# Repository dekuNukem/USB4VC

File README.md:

# USB4VC: USB Inputs on Retro Computers!

[Get USB4VC!](https://www.tindie.com/products/dekuNukem/usb4vc-usb-inputs-on-retro-computers/) | [Official Discord](https://discord.gg/HAuuh3pAmB) | [Getting Started](getting_started.md) | [Table of Contents](#table-of-contents)

-----

USB4VC is an **active protocol converter** that let you use **USB keyboard, mouse, and gamepads** on many different retro computers.

With a **modular design**, different platforms are supported by swapping out **Protocol Cards**:

USB4VC is [now available on Tindie](https://www.tindie.com/products/dekuNukem/usb4vc-usb-inputs-on-retro-computers/), with two Protocol Cards:

#### IBM PC Compatible

* PS/2 Keyboard (Scancode set 1, 2 and 3)
* PS/2 Mouse
* AT Keyboard
* XT Keyboard
* Microsoft Serial Mouse
* Mouse Systems Serial Mouse
* 15-pin Gameport Gamepad
* Mapping USB Gamepad to PC Mouse/Keyboard

From the very first IBM PC in 1981 until the end of PS/2 ports in early 2000s, this Protocol Card covers it all!

#### Apple Lisa, Early Macintosh, and Apple Desktop Bus (ADB)

* Apple Lisa Keyboard (A6MB101)
* Apple Lisa Mouse (A9M0050)
* Macintosh Keyboard (M0110A)
* Macintosh Mouse (M0100)
* ADB Keyboard
* ADB Mouse
* Mapping USB gamepad to all above

From Apple Lisa in 1983 to PowerMac G3 in 1999, and everything in-between!

#### More to Come!

Of course, more Protocol Cards are planned, and you can try [make your own](technical_notes.md) too!

## I Want One! / Get in Touch

USB4VC is now available [on my Tindie store](https://www.tindie.com/products/dekuNukem/usb4vc-usb-inputs-on-retro-computers/) after being successfully funded [on Kickstarter!](https://www.kickstarter.com/projects/dekunukem/usb4vc-usb-inputs-on-retro-computers)!

**Questions or comments?** Ask in [official Discord](https://discord.gg/HAuuh3pAmB), raise a [Github issue](https://github.com/dekuNukem/USB4VC/issues), [Twitter DM](https://twitter.com/dekuNukem_), or email `dekunukem` `gmail.com`!

## Videos

* [LGR Review](https://www.youtube.com/watch?v=tbHr7ULpusM)

* [Michael MJD Review](https://www.youtube.com/watch?v=Hv4A9p7Cn2s)

* [1Bit Fever Dreams review of Lisa/Mac/ADB card](https://youtu.be/ALm5LWS0fqU)

## Highlights

* USB Keyboard/Mouse/Gamepads on Vintage Computers!

* Modular & Swappable Protocol Cards

* Wireless / Bluetooth

* Ultra Low Latency (0.5ms)

* Fully Open-source

* Make-your-own Protocol Card [Instruction Provided](technical_notes.md)

## How it Works

USB4VC consists of two halves: **Baseboard** and swappable **Protocol Cards**.

Baseboard contains user buttons, OLED screen, and a Raspberry Pi. It processes USB input events, which are sent to Protocol Card.

Each Protocol Card has a dedicated microcontroller and connectors for a specific platform.

By splitting duties, RPi can focus on input parsing, and Protocol Card handles timing critical signal generation, resulting in a flexible architecture and reliable performance.

USB peripherals can be connected via cables, wireless dongles, or Bluetooth.

## Getting Started

[Click me](getting_started.md)

## Technical Details / Make Your Own Protocol Cards

[Click me](technical_notes.md)

## Why / Project Goals

Before the homogeneity of USB peripherals today, computer input devices were a wild west of proprietary peripherals, as different platforms used their own connectors and protocols for keyboards, mice, and gamepads.

With the popularity of retro computing today, it poses several issues:

* Many of those peripherals are simply **hard to find**, commanding a premium on online marketplaces. They are only getting rarer, and without them, the computer itself is useless.

* After decades of service, many can be **degraded and unreliable** (e.g. foam & foil keyboards), requiring extensive restoration.

* Many early peripherals simply **does not feel that great**. Mushy membrane keyboards, sticky ball mice, plasticky gamepads, etc. And of course, the good ones gets [*very expensive*](https://www.ebay.com/sch/i.html?_nkw=ibm+model+f&_sacat=0&rt=nc&LH_Sold=1&LH_Complete=1).

* On the other hand, good quality USB peripherals can be had for a very reasonable price today with vastly **superior tactility, precision, and ergonomics**.

* Thus, this project aims to make retro computers simply **more enjoyable to use**.

* I also hope it can **lower the barrier of entry** for certain machines, put more computers **back in action**, help **preserving** existing peripherals, and generally **help more people** get into this hobby!

But of course, one can argue that using period-correct peripherals is simply part of the hobby, but just like HDMI upscalers or floppy emus, it's nice to have the option to enhance the experience.

## Q&A

### Where can I get one?

This project have been successly funded [via Kickstarter!](https://www.kickstarter.com/projects/dekunukem/usb4vc-usb-inputs-on-retro-computers), now it is available [on my Tindie store!](https://www.tindie.com/products/dekuNukem/usb4vc-usb-inputs-on-retro-computers/)

### Which Raspberry Pi can I use?

Any RPi with a **40-pin header** *should* work, although **Model B/B+** is preferred. See [this table](https://en.wikipedia.org/wiki/Raspberry_Pi#Model_comparison) for details, sort by **GPIO** column.

USB4VC has been officially tested on **Raspberry Pi 2/3/4 Model B**.

Raspberry Pi Zeros should work too, but would need a USB hub.

No need to get the latest and greatest. An older RPi is plenty fast enough!

### What about latency?

0.5ms to 1ms depending on the Raspberry Pi generation.

1ms is *one thousandth* of a second. [More info here](technical_notes.md#latency-information).

### Can you develop a Protocol Card for ___ ?

I'd love to! But I would need a working machine with working peripherals.

So if you're in UK and is happy to lend me one for a while, [let me know!](#i-want-one--get-in-touch)

Also, as I can only work on so many at once, I'll probably focus on the more popular machines at first, but still, do let me know!

### Can I make my own Protocol Cards?

Of course! See [this document](technical_notes.md).

### What does USB4VC stand for?

USB for Vintage Computers. Although come to think of it, it's perfect for vintage consoles too! 🤔

## Questions or Comments?

Feel free to ask in official [Discord Chatroom](https://discord.gg/HAuuh3pAmB), raise a [Github issue](https://github.com/dekuNukem/USB4VC/issues), [DM on Twitter](https://twitter.com/dekuNukem_), or email `dekunukem` `gmail.com`!

## Table of Contents

[Main page](README.md)

[(Youtube Video) USB4VC in Action](https://www.youtube.com/watch?v=54sdPELuu4g)

[Getting Started Guide](getting_started.md)

[Kit Assembly Guide](kit_assembly.md)

[Tinkering Guide / Make Your Own Protocol Card / Technical Notes](technical_notes.md)

[Kickstarter Acknowledgements](kickstarter_info.md)

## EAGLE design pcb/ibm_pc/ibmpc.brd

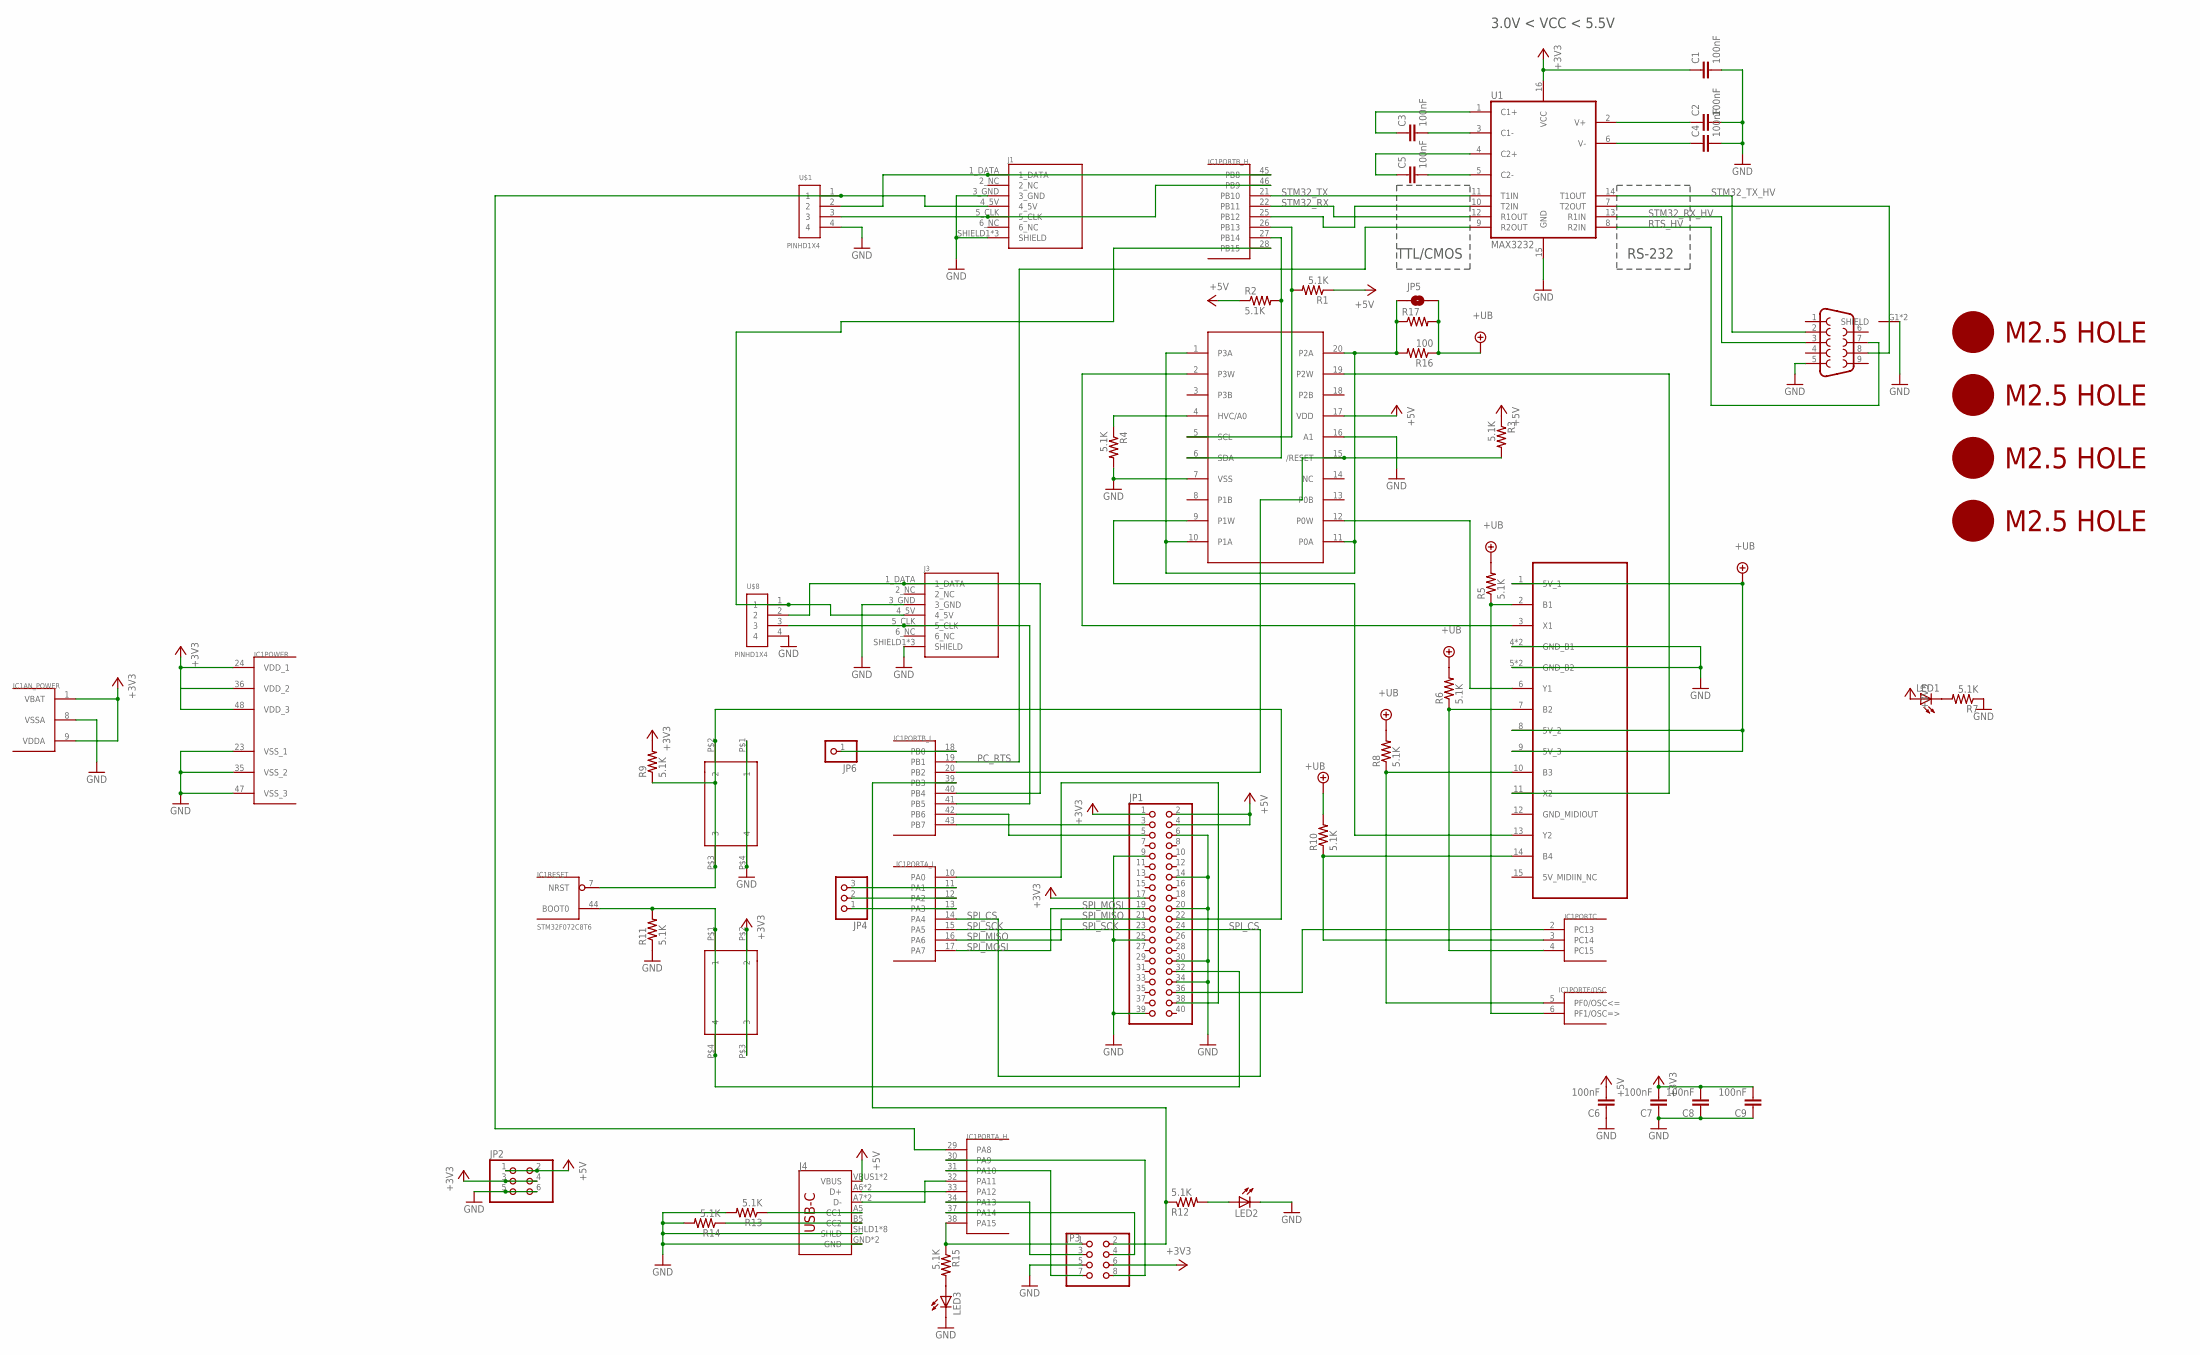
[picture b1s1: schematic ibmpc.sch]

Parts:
C1, C2, C3, C4, C5, C6, C7, C8, C9: 100nF; 0805@1
IC1: STM32F072C8T6; TQFP48
J1, J3: DIN7
J2: DB9MALE; DB9_MALE
J4: USB_C16PIN; USB-C-16P
JP1: PINHD-2X20-BIG; 2X20-BIG
JP2: PINHD-2X3; 2X03
JP3: PINHD-2X4; 2X04
JP4: PINHD-1X3CB; 1X03-CLEANBIG
JP5: JUMPER-SMT_2_NO_NO-SILK; SMT-JUMPER_2_NO_NO-SILK
JP6: PINHD-1X1CB; 1X01-CLEANBIG
LED1, LED2, LED3: LEDCHIP-LED0805; CHIP-LED0805
R1, R2, R3, R4, R5, R6, R7, R8, R9, R10, R11, R12, R13, R14, R15: 5.1K; 0805
R16: 100; 0805
R17: R-US_0204/7; 0204/7
SW1, SW2: 324_SW; 342_SWICH_FOOT
U1: MAX3232; SO016
U$1, U$8: PINHD1X4; 1X04-CLEANBIG
U$2, U$3, U$6, U$7: M2.5HOLE
U$5: MCP4451; TSSOP20
U$9: GAMEPORT_15P; DA15

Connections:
+3V3: C1.1, C7.2, C8.2, C9.2, IC1.1 (VBAT), IC1.9 (VDDA), IC1.24 (VDD_1), IC1.36 (VDD_2), IC1.48 (VDD_3), JP1.1, JP1.17, JP2.3, JP2.4, JP3.6, LED1.A, R9.2, SW2.P$2 (2), SW2.P$3 (3), U1.16 (VCC)
+5V: C6.2, J4.VBUS1 (VBUS), J4.VBUS2 (VBUS), JP1.2, JP1.4, JP2.1, JP2.2, R1.1, R2.1, R3.1, U$5.17 (VDD)
+UB: JP5.2, R5.2, R6.2, R8.2, R10.2, R16.1, R17.2, U$9.1 (5V_1), U$9.8 (5V_2), U$9.9 (5V_3)
C1+: C3.1, U1.1 (C1+)
C1-: C3.2, U1.3 (C1-)
C2+: C5.1, U1.4 (C2+)
C2-: C5.2, U1.5 (C2-)
GND: C1.2, C2.2, C4.2, C6.1, C7.1, C8.1, C9.1, IC1.8 (VSSA), IC1.23 (VSS_1), IC1.35 (VSS_2), IC1.47 (VSS_3), J1.3_GND, J1.SHIELD1 (SHIELD), J1.SHIELD2 (SHIELD), J1.SHIELD3 (SHIELD), J2.5, J2.G1 (SHIELD), J2.G2 (SHIELD), J3.3_GND, J3.SHIELD1 (SHIELD), J3.SHIELD2 (SHIELD), J3.SHIELD3 (SHIELD), J4.GND, J4.GND2 (GND), J4.SHLD1 (SHLD), J4.SHLD2 (SHLD), J4.SHLD3 (SHLD), J4.SHLD4 (SHLD), J4.SHLD5 (SHLD), J4.SHLD6 (SHLD), J4.SHLD7 (SHLD), J4.SHLD8 (SHLD), JP1.6, JP1.9, JP1.14, JP1.20, JP1.25, JP1.30, JP1.34, JP1.39, JP2.5, JP2.6, JP3.5, LED2.C, LED3.C, R4.2, R7.1, R11.1, R13.2, R14.2, SW1.P$1 (1), SW1.P$4 (4), U1.15 (GND), U$1.4, U$5.7 (VSS), U$5.16 (A1), U$8.4, U$9.4 (GND_B1), U$9.5 (GND_B2), U$9.G1 (GND_B1), U$9.G2 (GND_B2)
unnamed: J4.A5 (CC1), R13.1
unnamed: LED2.A, R12.2
unnamed: IC1.10 (PA0), JP1.38
unnamed: IC1.29 (PA8), J1.4_5V, U$1.1
unnamed: IC1.41 (PB5), J3.5_CLK, U$8.3
unnamed: IC1.39 (PB3), JP3.2, R12.1
unnamed: J4.B5 (CC2), R14.1
unnamed: IC1.33 (PA12), J4.A6 (D+), J4.B6 (D+)
unnamed: IC1.32 (PA11), J4.A7 (D-), J4.B7 (D-)
unnamed: IC1.45 (PB8), J1.1_DATA, U$1.2
unnamed: IC1.46 (PB9), J1.5_CLK, U$1.3
unnamed: IC1.31 (PA10), JP3.7
unnamed: IC1.7 (NRST), JP1.22, R9.1, SW1.P$2 (2), SW1.P$3 (3)
unnamed: IC1.30 (PA9), JP3.8
unnamed: IC1.34 (PA13), JP3.3
unnamed: IC1.37 (PA14), JP3.4
unnamed: JP5.1, R16.2, R17.1, U$5.1 (P3A), U$5.10 (P1A), U$5.11 (P0A), U$5.20 (P2A)
unnamed: IC1.44 (BOOT0), JP1.32, R11.2, SW2.P$1 (1), SW2.P$4 (4)
unnamed: IC1.4 (PC15), R6.1, U$9.7 (B2)
unnamed: IC1.5 (PF0/OSC<=), R8.1, U$9.10 (B3)
unnamed: IC1.3 (PC14), R10.1, U$9.14 (B4)
unnamed: IC1.42 (PB6), JP1.5
unnamed: IC1.43 (PB7), JP1.3
unnamed: IC1.25 (PB12), U1.10 (T2IN)
unnamed: J2.8, U1.7 (T2OUT)
unnamed: IC1.40 (PB4), J3.1_DATA, U$8.2
unnamed: IC1.38 (PA15), JP3.1, R15.1
unnamed: LED3.A, R15.2
unnamed: LED1.C, R7.2
unnamed: IC1.18 (PB0), JP6.1
unnamed: IC1.6 (PF1/OSC=>), R5.1, U$9.2 (B1)
unnamed: R4.1, U$5.4 (HVC/A0)
unnamed: IC1.2 (PC13), JP1.36
unnamed: IC1.11 (PA1), JP4.3
unnamed: IC1.12 (PA2), JP4.2
unnamed: IC1.13 (PA3), JP4.1
unnamed: IC1.28 (PB15), J3.4_5V, U$8.1
unnamed: IC1.20 (PB2), R3.2, U$5.15 (/RESET)
PC_RTS: IC1.19 (PB1), U1.9 (R2OUT)
POT_SCL: IC1.26 (PB13), R1.2, U$5.5 (SCL)
PST_SDA: IC1.27 (PB14), R2.2, U$5.6 (SDA)
RTS_HV: J2.7, U1.8 (R2IN)
SPI_CS: IC1.14 (PA4), JP1.24
SPI_MISO: IC1.16 (PA6), JP1.21
SPI_MOSI: IC1.17 (PA7), JP1.19
SPI_SCK: IC1.15 (PA5), JP1.23
STM32_RX: IC1.22 (PB11), U1.12 (R1OUT)
STM32_RX_HV: J2.3, U1.13 (R1IN)
STM32_TX: IC1.21 (PB10), U1.11 (T1IN)
STM32_TX_HV: J2.2, U1.14 (T1OUT)
V+: C2.1, U1.2 (V+)
V-: C4.1, U1.6 (V-)
X1_W3: U$5.2 (P3W), U$9.3 (X1)
X2_W2: U$5.19 (P2W), U$9.11 (X2)
Y1_W0: U$5.12 (P0W), U$9.6 (Y1)
Y2_W1: U$5.9 (P1W), U$9.13 (Y2)

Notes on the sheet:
RS-232
TTL/CMOS
3.0V < VCC < 5.5V

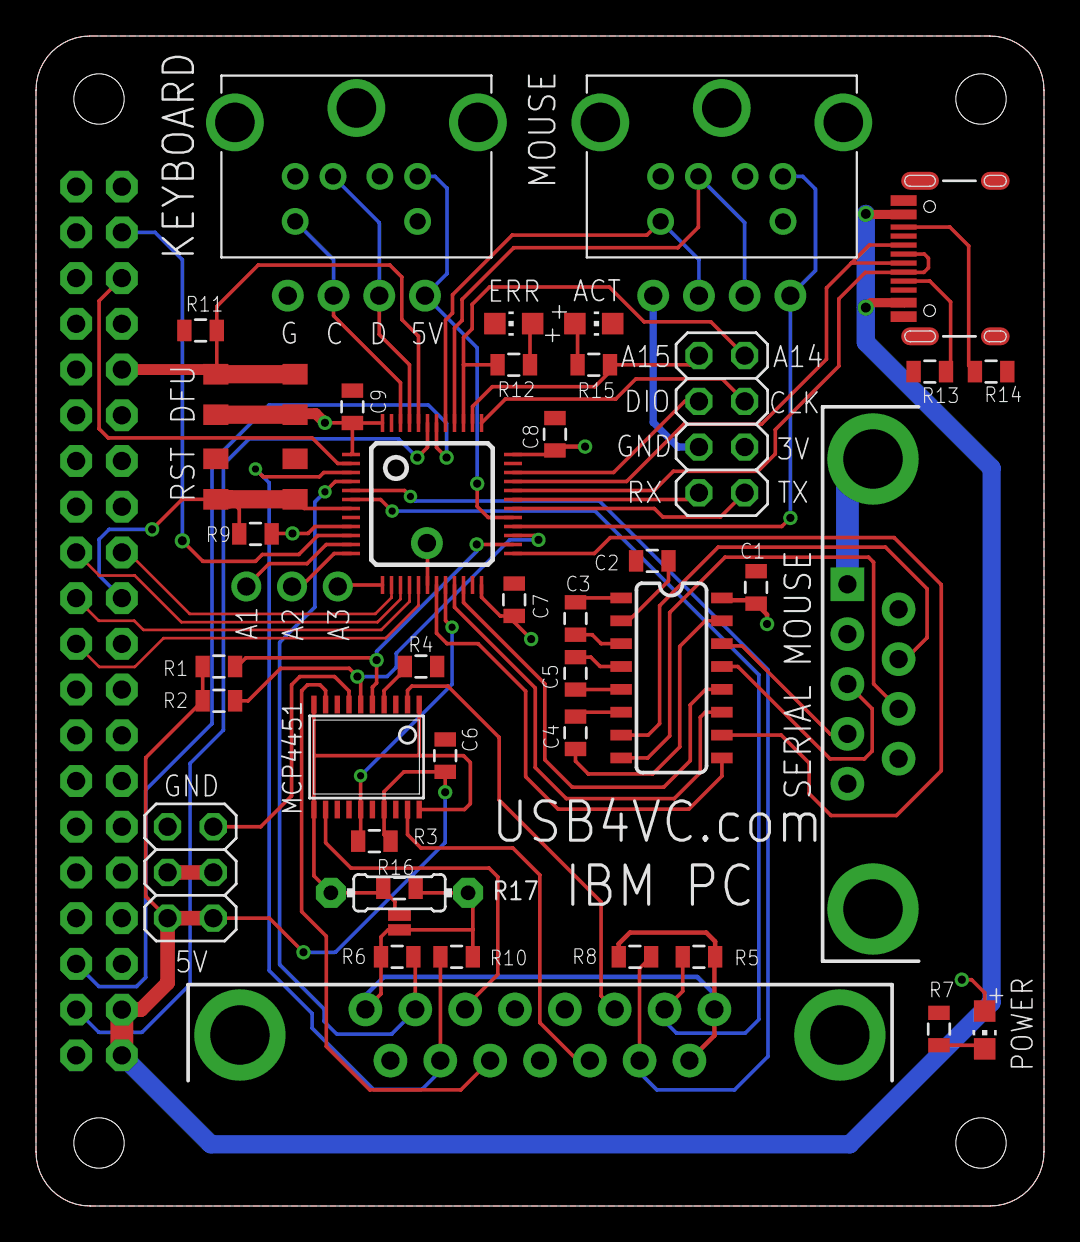
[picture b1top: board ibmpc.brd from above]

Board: 2 copper layers, 56.0 x 65.0 mm, 51 parts (1 on the bottom side), 64 nets.

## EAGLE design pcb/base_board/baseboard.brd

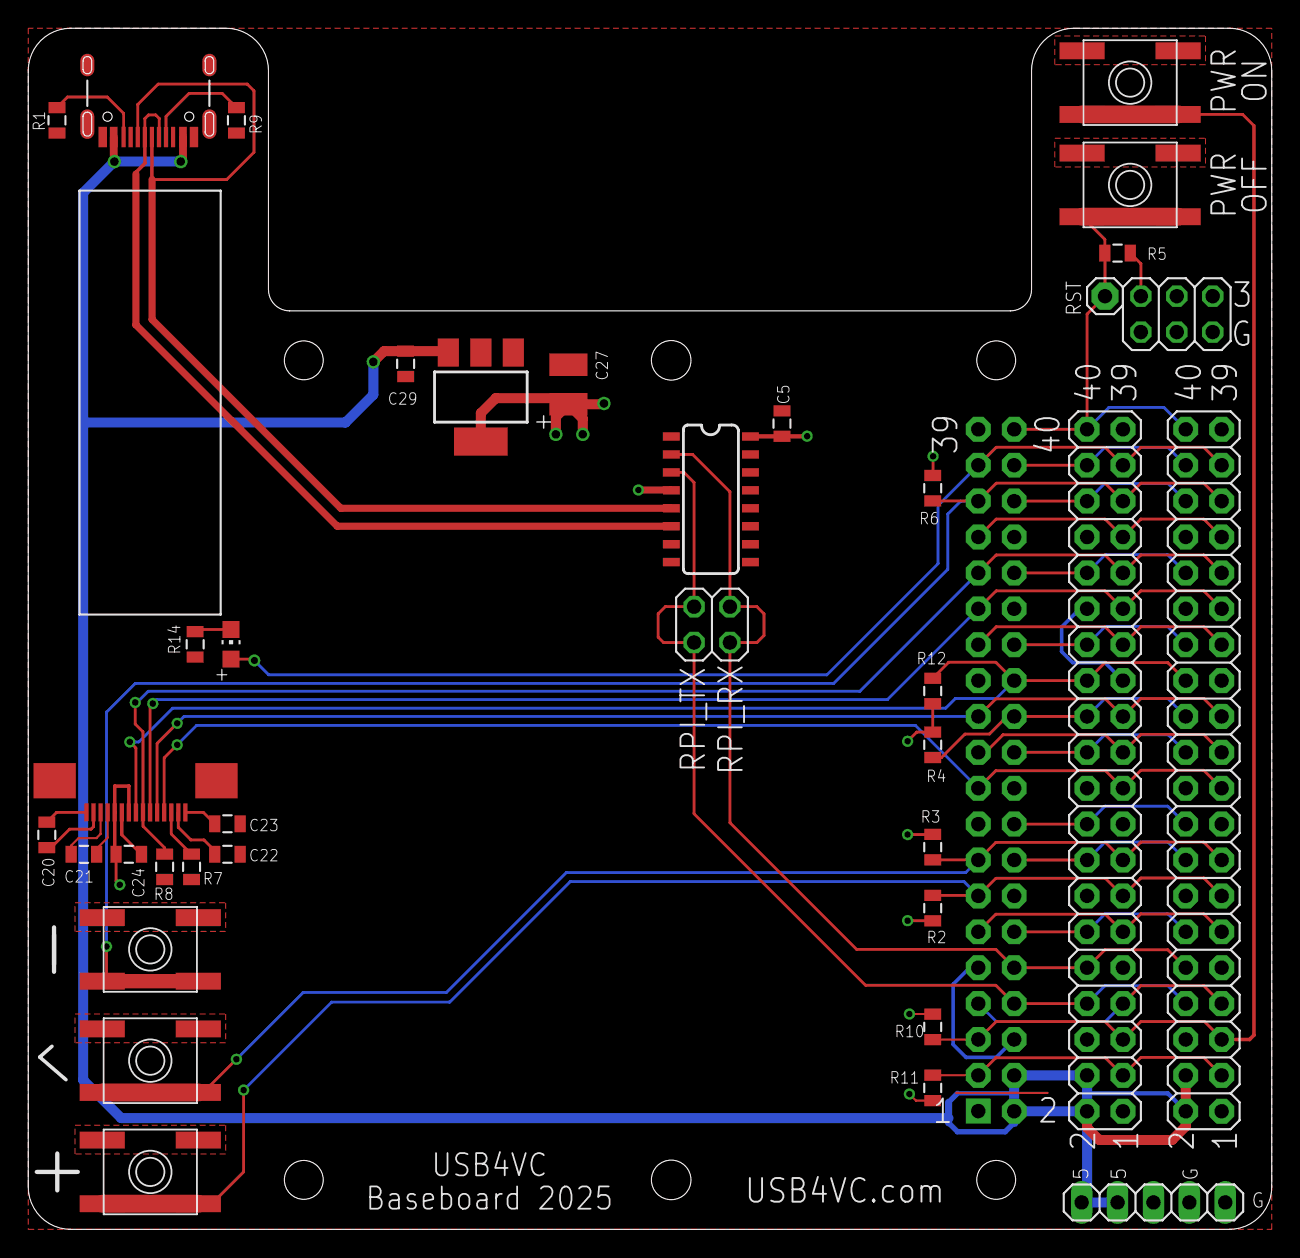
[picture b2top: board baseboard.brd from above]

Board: 2 copper layers, 88.0 x 85.0 mm, 40 parts (0 on the bottom side), 43 nets.

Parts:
C5, C24: 100nF; 0805
C20, C21: 1uF; 0805
C22, C23, C29: 2.2uF; 0805
C27: 47uF; C1210
IC1: LD117AS33TR; SOT223
J2: USB-C-16P
JP3: 1X01
JP5: 1X05
JP6: 2X03
JP7: 2X02
LED1: CHIP-LED0805
P1: RPI3NO-CONNECTORS; RPI3-NO-CONNECTORS
P2, P3: 2X20-BIG
R1, R2, R3, R4, R5, R6, R8, R9, R10, R11, R12: 5.1K; 0805
R7: 390K; 0805
R14: 2K; 0805
SW2, SW5, SW6, SW7, SW8: SPST_TACT-EVQQ2; EVQ-Q2
U2: LUL_UG-2864HSWEG01_1.3_WRAPAROUND
U5: CH340C; SO016
U$2, U$3: M2.5HOLE

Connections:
+3V3: C5.2, C24.2, C27.1, IC1.4, JP6.2, JP6.4, JP6.6, P2.1, P2.17, P3.1, P3.17, R2.2, R3.2, R4.1, R5.2, R6.2, R10.1, R11.1, R12.1, U2.5, U2.7, U5.4, U5.16
+5V: C29.2, IC1.3, J2.VBUS1, J2.VBUS2, JP5.1, JP5.2, P1.P$2, P1.P$4, P2.2, P2.4, P3.2, P3.4
ENTER_BUTTON: P1.P$15, P2.15, P3.15, R3.1, SW6.A, SW6.A'
GND: C5.1, C22.1, C23.1, C24.1, C27.2, C29.1, IC1.1, J2.GND, J2.GND2, J2.SHLD1, J2.SHLD2, J2.SHLD3, J2.SHLD4, J2.SHLD5, J2.SHLD6, J2.SHLD7, J2.SHLD8, JP5.4, JP5.5, JP6.1, JP6.3, JP6.5, P1.P$6, P1.P$9, P1.P$14, P1.P$20, P1.P$25, P1.P$30, P1.P$34, P1.P$39, P2.6, P2.9, P2.14, P2.20, P2.25, P2.30, P2.34, P2.39, P3.6, P3.9, P3.14, P3.20, P3.25, P3.30, P3.34, P3.39, R1.2, R7.1, R8.2, R9.2, R14.1, SW2.A, SW2.A', SW5.B, SW5.B', SW6.B, SW6.B', SW7.B, SW7.B', SW8.B, SW8.B', U2.6, U2.16, U2.17, U5.1
MINUS_BUTTON: P1.P$35, P2.35, P3.35, R6.1, SW5.A, SW5.A'
unnamed: J2.A6, J2.B6, U5.5
unnamed: J2.A5, R9.1
unnamed: J2.A7, J2.B7, U5.6
unnamed: LED1.A, P1.P$37, P2.37, P3.37
unnamed: P1.P$3, P2.3, P3.3, R11.2
unnamed: P1.P$5, P2.5, P3.5, R10.2, SW8.A, SW8.A'
unnamed: J2.B5, R1.1
unnamed: P1.P$7, P2.7, P3.7
unnamed: P1.P$11, P2.11, P3.11
unnamed: LED1.C, R14.2
unnamed: P1.P$19, P2.19, P3.19, U2.12
unnamed: P1.P$21, P2.21, P3.21
unnamed: P1.P$23, P2.23, P3.23, U2.11
unnamed: P1.P$27, P2.27, P3.27
unnamed: P1.P$29, P2.29, P3.29, U2.10
unnamed: P1.P$33, P2.33, P3.33
unnamed: P1.P$12, P2.12, P3.12
unnamed: P1.P$16, P2.16, P3.16
unnamed: P1.P$18, P2.18, P3.18
unnamed: P1.P$22, P2.22, P3.22
unnamed: P1.P$24, P2.24, P3.24, R4.2
unnamed: P1.P$26, P2.26, P3.26, R12.2, U2.8
unnamed: P1.P$28, P2.28, P3.28
unnamed: P1.P$32, P2.32, P3.32
unnamed: P1.P$36, P2.36, P3.36
unnamed: P1.P$38, P2.38, P3.38
unnamed: JP3.1, P1.P$40, P2.40, P3.40, R5.1, SW2.B, SW2.B'
unnamed: C20.2, U2.1
unnamed: C20.1, U2.2
unnamed: C21.2, U2.3
unnamed: C21.1, U2.4
unnamed: R7.2, U2.13
unnamed: C22.2, U2.14
unnamed: C23.2, U2.15
unnamed: P1.P$31, P2.31, P3.31, R8.1, U2.9
PLUS_BUTTON: P1.P$13, P2.13, P3.13, R2.1, SW7.A, SW7.A'
RPI_RX: JP7.1, JP7.2, P1.P$10, P2.10, P3.10, U5.2
RPI_TX: JP7.3, JP7.4, P1.P$8, P2.8, P3.8, U5.3

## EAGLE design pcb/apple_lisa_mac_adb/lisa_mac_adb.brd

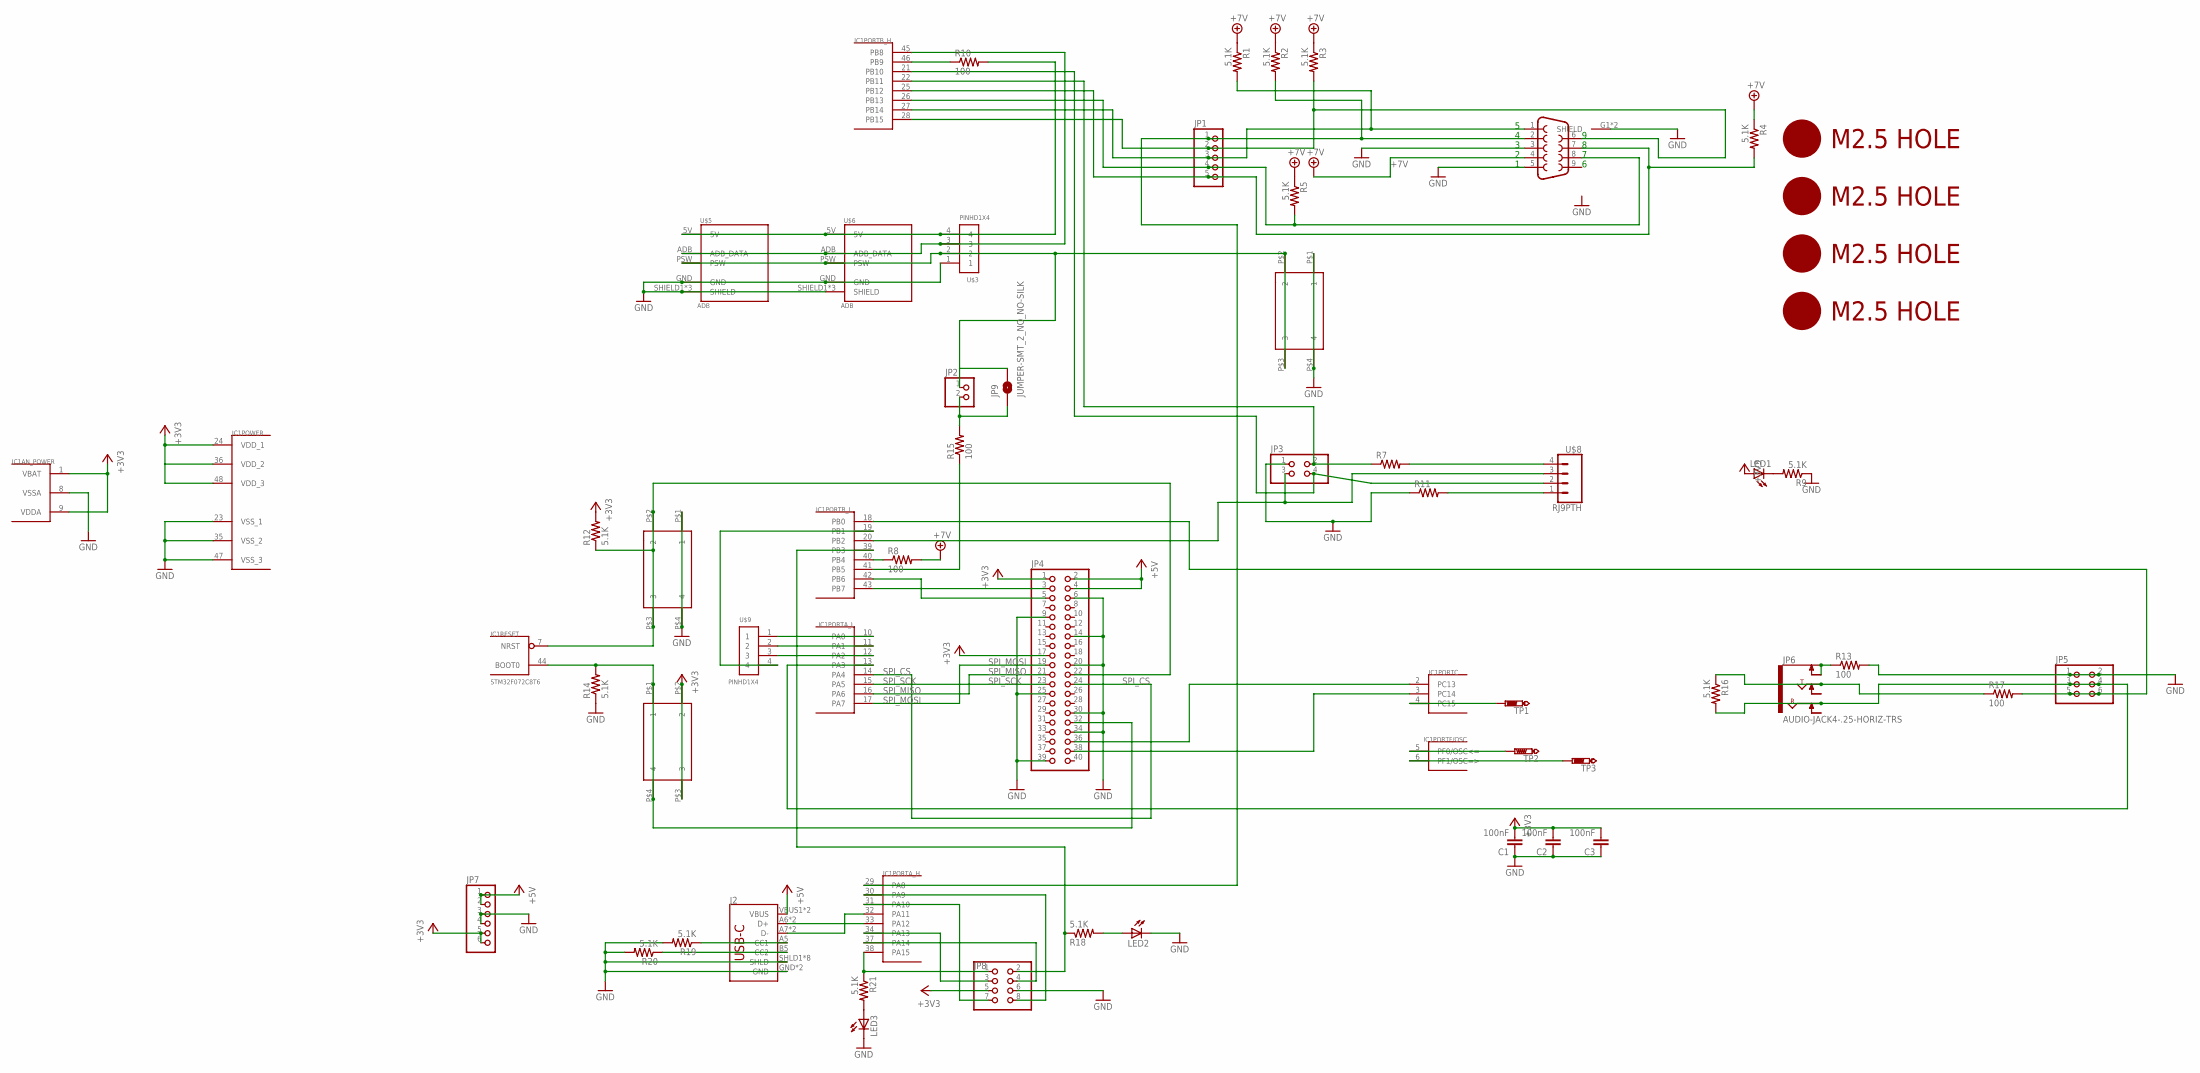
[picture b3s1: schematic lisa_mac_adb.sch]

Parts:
C1, C2, C3: 100nF; 0805@1
IC1: STM32F072C8T6; TQFP48
J1: DB9FEMALE; DB9
J2: USB_C16PIN; USB-C-16P
JP1: PINHD-1X5; 1X05
JP2: PINHD-1X2; 1X02
JP3: PINHD-2X2; 2X02
JP4: PINHD-2X20-BIG; 2X20-BIG
JP5: PINHD-2X3; 2X03
JP6: AUDIO-JACK4-.25-HORIZ-TRS; AUDIO-JACK-.25-INCH-HORIZ-PTH
JP7: PINHD-1X6CB; 1X06-CLEANBIG
JP8: PINHD-2X4; 2X04
JP9: JUMPER-SMT_2_NO_NO-SILK; SMT-JUMPER_2_NO_NO-SILK
LED1, LED2, LED3: LEDCHIP-LED0805; CHIP-LED0805
R1, R2, R3, R4, R5, R9, R12, R14, R16, R18, R19, R20, R21: 5.1K; 0805
R7, R8, R10, R11, R13, R15, R17: 100; 0805
SW1, SW2, SW3: 324_SW; 342_SWICH_FOOT
TP1, TP2, TP3: PTR1TP14R; TP14R
U$1, U$2, U$4, U$7: M2.5HOLE
U$3, U$9: PINHD1X4; 1X04-CLEANBIG
U$5, U$6: ADB; DIN4
U$8: RJ9PTH; RJ9

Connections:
+3V3: C1.2, C2.2, C3.2, IC1.1 (VBAT), IC1.9 (VDDA), IC1.24 (VDD_1), IC1.36 (VDD_2), IC1.48 (VDD_3), JP4.1, JP4.17, JP7.5, JP7.6, JP8.5, LED1.A, R12.2, SW3.P$2 (2), SW3.P$3 (3)
+5V: J2.VBUS1 (VBUS), J2.VBUS2 (VBUS), JP4.2, JP4.4, JP7.1, JP7.2
+7V: J1.4, R1.1, R2.1, R3.1, R4.1, R5.1, R8.2
GND: C1.1, C2.1, C3.1, IC1.8 (VSSA), IC1.23 (VSS_1), IC1.35 (VSS_2), IC1.47 (VSS_3), J1.3, J1.5, J1.G1 (SHIELD), J1.G2 (SHIELD), J2.GND, J2.GND2 (GND), J2.SHLD1 (SHLD), J2.SHLD2 (SHLD), J2.SHLD3 (SHLD), J2.SHLD4 (SHLD), J2.SHLD5 (SHLD), J2.SHLD6 (SHLD), J2.SHLD7 (SHLD), J2.SHLD8 (SHLD), JP3.1, JP4.6, JP4.9, JP4.14, JP4.20, JP4.25, JP4.30, JP4.34, JP4.39, JP5.1, JP5.2, JP7.3, JP7.4, JP8.6, LED2.C, LED3.C, R9.1, R11.1, R13.2, R14.1, R19.2, R20.2, SW1.P$1 (1), SW1.P$4 (4), SW2.P$1 (1), SW2.P$4 (4), U$3.1, U$5.GND, U$5.SHIELD1 (SHIELD), U$5.SHIELD2 (SHIELD), U$5.SHIELD3 (SHIELD), U$6.GND, U$6.SHIELD1 (SHIELD), U$6.SHIELD2 (SHIELD), U$6.SHIELD3 (SHIELD)
unnamed: J2.A5 (CC1), R19.1
unnamed: LED2.A, R18.2
unnamed: R10.2, U$3.4, U$5.5V, U$6.5V
unnamed: IC1.26 (PB13), J1.8, JP1.4, R5.2
unnamed: R7.2, U$8.4
unnamed: IC1.39 (PB3), JP8.2, R18.1
unnamed: J2.B5 (CC2), R20.1
unnamed: IC1.33 (PA12), J2.A6 (D+), J2.B6 (D+)
unnamed: IC1.32 (PA11), J2.A7 (D-), J2.B7 (D-)
unnamed: IC1.41 (PB5), R15.1
unnamed: IC1.19 (PB1), U$9.4
unnamed: IC1.31 (PA10), JP8.7
unnamed: IC1.7 (NRST), JP4.22, R12.1, SW2.P$2 (2), SW2.P$3 (3)
unnamed: IC1.30 (PA9), JP8.8
unnamed: IC1.34 (PA13), JP8.3
unnamed: IC1.37 (PA14), JP8.4
unnamed: IC1.22 (PB11), JP3.2, R7.1
unnamed: IC1.44 (BOOT0), JP4.32, R14.2, SW3.P$1 (1), SW3.P$4 (4)
unnamed: IC1.21 (PB10), JP3.4, U$8.2
unnamed: IC1.4 (PC15), TP1.TP
unnamed: R11.2, U$8.1
unnamed: IC1.42 (PB6), JP4.5
unnamed: IC1.43 (PB7), JP4.3
unnamed: JP6.SLEEVE (EARTH), JP6.SLEEVE-NORM (EARTH-NORM), R13.1
unnamed: IC1.20 (PB2), JP3.3, U$8.3
unnamed: IC1.27 (PB14), J1.1, JP1.3, R1.2
unnamed: IC1.38 (PA15), JP8.1, R21.1
unnamed: LED3.A, R21.2
unnamed: LED1.C, R9.2
unnamed: IC1.13 (PA3), JP5.3, JP5.4, JP6.RING, R16.2
unnamed: IC1.18 (PB0), JP5.5, JP5.6, R17.2
unnamed: JP6.TIP, R16.1, R17.1
unnamed: IC1.3 (PC14), JP4.38
unnamed: IC1.28 (PB15), J1.6, JP1.2, R3.2
unnamed: IC1.25 (PB12), J1.7, JP1.5, R4.2
unnamed: IC1.29 (PA8), J1.2, JP1.1, R2.2
unnamed: IC1.2 (PC13), JP4.36
unnamed: IC1.10 (PA0), U$9.1
unnamed: IC1.11 (PA1), U$9.2
unnamed: IC1.12 (PA2), U$9.3
unnamed: IC1.5 (PF0/OSC<=), TP2.TP
unnamed: IC1.6 (PF1/OSC=>), TP3.TP
unnamed: IC1.45 (PB8), U$3.3, U$5.ADB (ADB_DATA), U$6.ADB (ADB_DATA)
unnamed: IC1.40 (PB4), R8.1
unnamed: IC1.46 (PB9), R10.1
unnamed: JP2.1, JP9.2, SW1.P$2 (2), SW1.P$3 (3), U$3.2, U$5.PSW, U$6.PSW
unnamed: JP2.2, JP9.1, R15.2
SPI_CS: IC1.14 (PA4), JP4.24
SPI_MISO: IC1.16 (PA6), JP4.21
SPI_MOSI: IC1.17 (PA7), JP4.19
SPI_SCK: IC1.15 (PA5), JP4.23

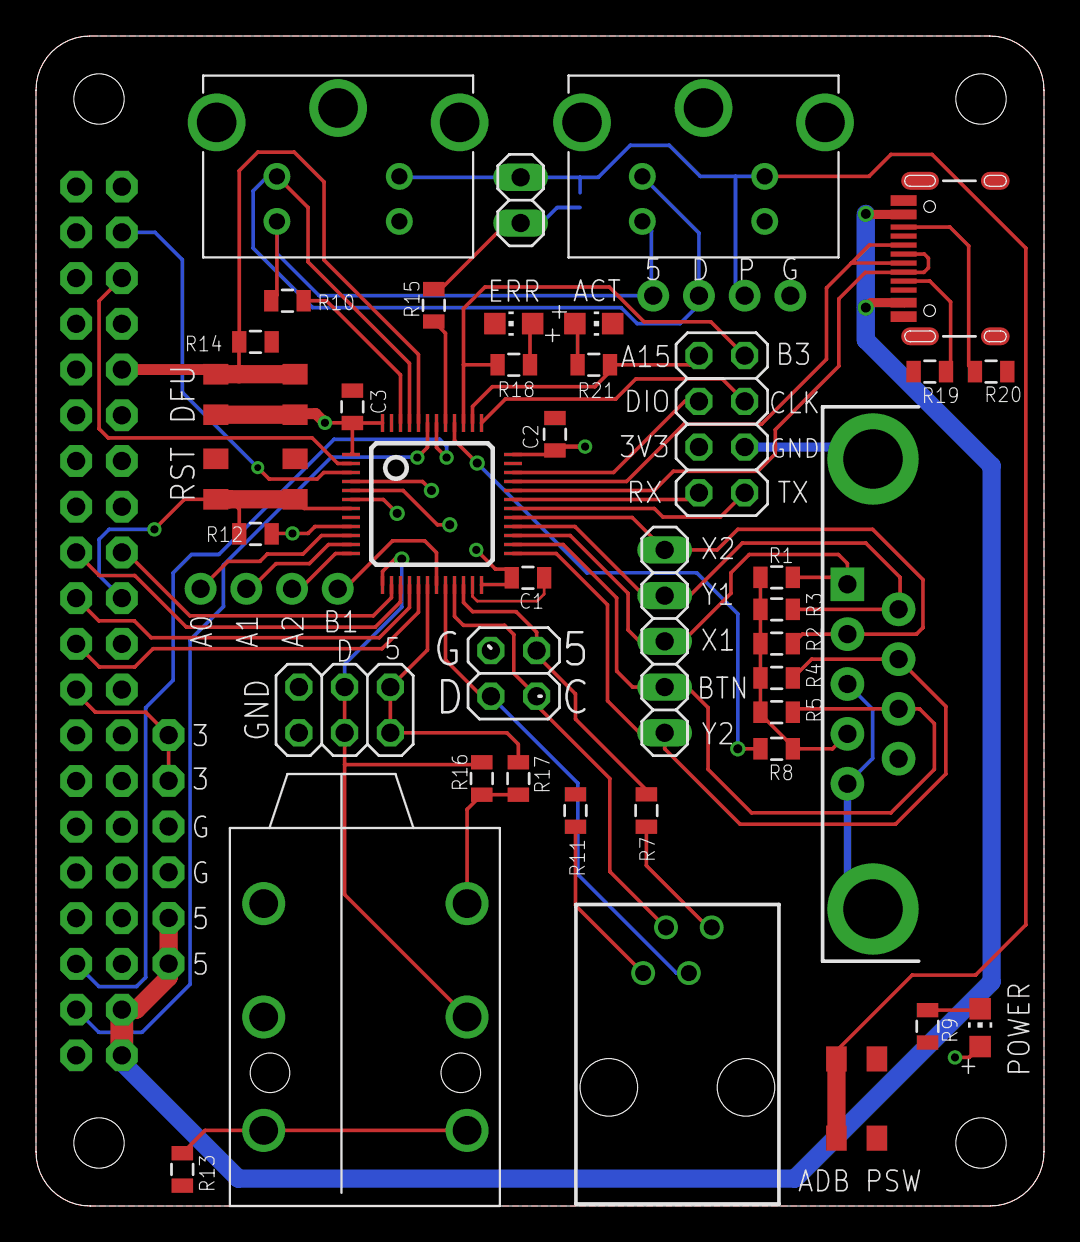
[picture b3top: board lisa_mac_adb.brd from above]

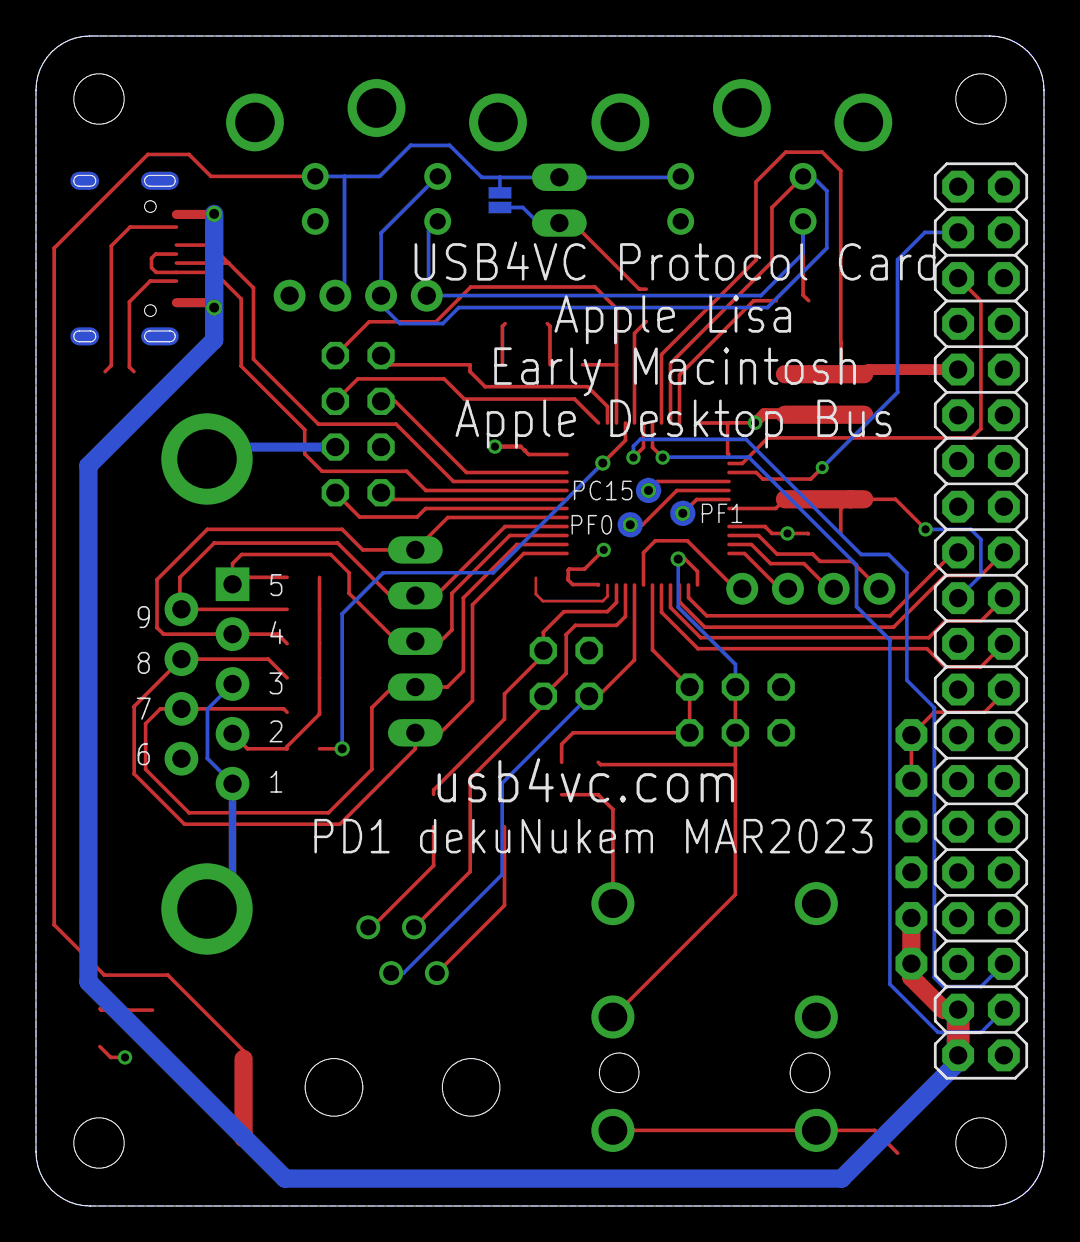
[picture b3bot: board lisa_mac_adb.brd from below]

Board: 2 copper layers, 56.0 x 65.0 mm, 53 parts (5 on the bottom side), 55 nets.

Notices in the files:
parts and their libraries:
SparkFun-Connectors: Licensing: Creative Commons ShareAlike 4.0 International - https://creativecommons.org/licenses/by-sa/4.0
SparkFun-Aesthetics: Licensing: CC v3.0 Share-Alike You are welcome to use this library for commercial purposes.
SparkFun-Aesthetics: Released under the Creative Commons
